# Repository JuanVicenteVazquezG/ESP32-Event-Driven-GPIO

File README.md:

# ESP32 Event-Driven GPIO Controller

**Resilient Digital Input System for Industrial Environments.**

This repository implements a High-Performance HAL (Hardware Abstraction Layer) for ESP32 GPIO management, focusing on strict C++20 standards and rigorous engineering practices.

## Core Features

* **Industrial Resilience:** Hybrid debouncing architecture combining physical RC filters with software-based hysteresis to eliminate noise in harsh electrical environments.
* **Low-Latency ISRs:** Interrupt Service Routines marked with `IRAM_ATTR` to ensure execution from RAM, minimizing latency and preventing cache misses during critical events.
* **Autonomous Recovery:** Self-healing logic designed to operate independently of the USB/Serial interface, ensuring system stability even after communication bus failures.
* **Non-Blocking Architecture:** Fully asynchronous event handling to maximize CPU cycles for RTOS tasks or networking stacks.

## Tech Stack
* **Language:** C++20 (GCC 13+)
* **Hardware:** ESP32 (Xtensa LX6)
* **Pattern:** Event-Driven / RAII / volatile states

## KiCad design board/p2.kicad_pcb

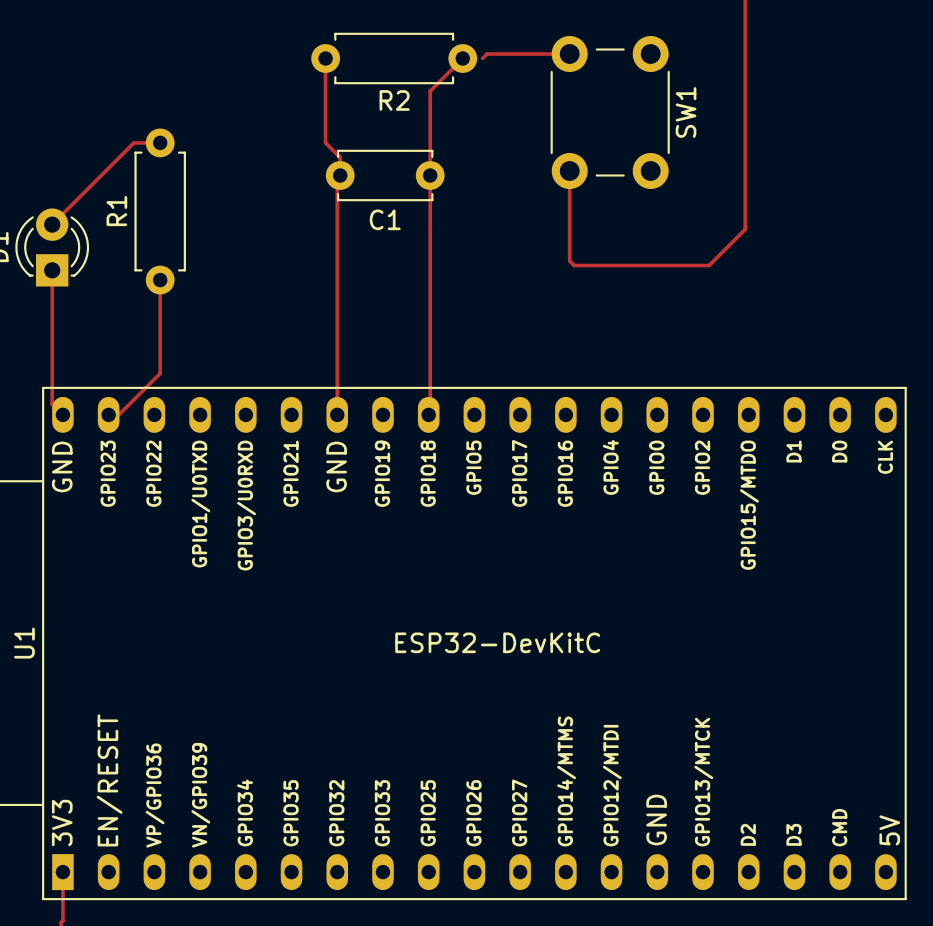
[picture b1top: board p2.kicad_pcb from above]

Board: 2 copper layers, 6 parts (0 on the bottom side), 5 nets.

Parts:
C1: C; C_Disc_D5.0mm_W2.5mm_P5.00mm
D1: LED; LED_D3.0mm
R1, R2: R; R_Axial_DIN0207_L6.3mm_D2.5mm_P7.62mm_Horizontal
SW1: SW_Push; SW_PUSH_6mm
U1: ESP32-DevKitC

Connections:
+3.3V: SW1.2, U1.1 (3V3)
GND: C1.2, D1.1 (K), R2.2, U1.14 (GND), U1.32 (GND), U1.38 (GND)
unnamed: D1.2 (A), R1.2
unnamed: C1.1, R2.1, SW1.1, U1.30 (GPIO18)
unnamed: R1.1, U1.37 (GPIO23)

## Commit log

2026-02-01 Add project overview to README.md
2026-02-01 First commit completed
2026-02-01 fix(gpio): solve state desync by reading hardware in ISR
